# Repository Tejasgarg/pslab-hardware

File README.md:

# PSLab-Mini-hardware

This branch is dedicated to prototyping the PSLab-Mini board and push out a working board that has functionalities of oscilloscope, multimeter and if time allows it, a logic analyser.

## PCB Layout
* I made a new PCB layout by first updating and removing components from the PSLab Schematic.
* The changed schematic was imported into a fresh PCB editor file in KiCAD.
* Made new edge cuts that provide a smaller footprint to the board compared to the current board
* Placed all the components and made a 4-layer PCB
* The 4 layers are as follows:
     * F.Cu(Front Copper) - Consists of signal routings
     * GND(Ground) - Consists of a ground pour in the entire layer
     * VDDA(Power) - Consists of a copper pour that transmits power to the majority of the components
     * B.Cu(Bottom Copper) - Also consists of the routing
* Used both through and buried vias:
     * Buried Vias - Used buried vias for connecting the components to the ground and power layer
     * Through Vias - Used Through vias for connecting the top and bottom copper layer for essentially connecting and routing wherever there was a blockage 
       due to already present routes

Front Side                        | Back Side
 -------------------------------- | ----------------------------------
 | 

## New Schematic
The new schematic has been made on top of the current schematic for a quicker prototype and clearly shows all the components removed in the current PSLab board, and explains the reasoning behind the removal of each. 

## Platform

* Microcontroller Platform : [PIC24EP256GP204](http://www.microchip.com/wwwproducts/en/PIC24EP256GP204)
* IDE: [MPLABX IDE v3.35](http://www.microchip.com/mplab/mplab-x-ide) (Supported on Linux/Windows/Mac)
* Compiler: [MPLAB® XC16 Compiler](http://www.microchip.com/mplab/compilers)
* Programming Tool: [PICkit™ 3 In-Circuit Debugger](http://www.microchip.com/Developmenttools/ProductDetails.aspx?PartNO=PG164130)

## New parts list

* [PIC24EP256GP204](http://www.microchip.com/wwwproducts/en/PIC24EP256GP204) - Microcontroller
* [MCP6S21](http://www.microchip.com/wwwproducts/en/mcp6s21) - Programmable gain amplifier
* [TL082](http://www.ti.com/product/TL082) - 2 channel Op-Amp
* [CP2102N-A02-GQFN24](https://www.silabs.com/documents/public/data-sheets/cp2102n-datasheet.pdf) - USB-UART bridge
* [SP0503BAHTG](https://m.littelfuse.com/~/media/electronics/datasheets/tvs_diode_arrays/littelfuse_tvs_diode_array_sp05_datasheet.pdf.pdf) - ESD protector

* 0.5 A Fuse
* Assorted resistors, capacitors & diodes

## Hardware Specs

* 3-Channel up to 2MSPS Oscilloscope. Software selectable amplification stages
* 12-bit Voltmeter. Input ranges from +/-10 mV to +/-16 V
* Capacitance Measurement. pF to uF range
* UART data buses for secondary modules 

## Feature list for PSLab-Mini

### Oscilloscopes

One of the main features of PSLab is the 3-channel Oscilloscope, which can monitor analog inputs at a maximum of 2 million samples per second.
In PSLab mini, this will be retained but with the following changes:
* Reduce the channels from 3 to 2 channels oscilloscope to reduce the components and cost
* Aim at increasing the max sampling rate

### Measurement Functions

* Frequency counter tested up to 16 MHz.
* Capacitance Measurement. pF to uF range
* Resistance measurement
* Voltmeter with a range of +/-10 mV to +/-16 V

### Other useful tools

* UART outputs
* Graphical Interfaces for Oscilloscope, Multimeter, streaming data and several experiments developed that use a common framework which drastically reduces code required to incorporate control and plotting widgets.

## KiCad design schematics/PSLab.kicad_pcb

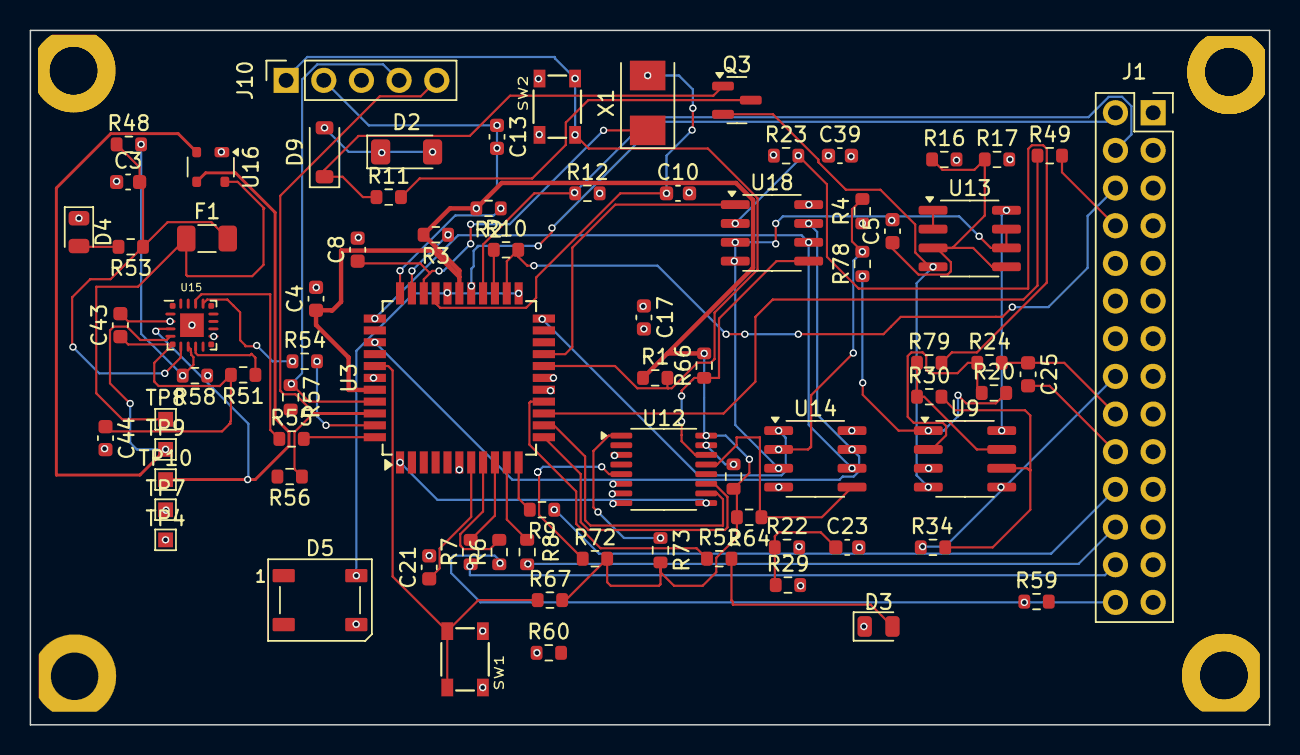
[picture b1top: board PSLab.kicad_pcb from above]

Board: 4 copper layers, 83.6 x 46.8 mm, 82 parts (0 on the bottom side), 71 nets.

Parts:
C3, C4, C13, C17, C25, C39, C43: 100nF; C_0603_1608Metric
C5, C23: 10nF; C_0603_1608Metric
C8, C10: 12pF; C_0603_1608Metric
C21, C44: 10uF; C_0603_1608Metric
D2: 6.8V; D_MiniMELF
D3: GREEN; LED_0805_2012Metric
D4: BLUE; LED_0805_2012Metric
D5: WS2812B; LED_WS2812B_PLCC4_5.0x5.0mm_P3.2mm
D9: 1N4148W; D_SOD-123
F1: 1A; Fuse_1206_3216Metric
J1: DoublePins; PinSocket_2x14_P2.54mm_Vertical
J10: Programmer; PinSocket_1x05_P2.54mm_Vertical
MH4, MH4#2, MH4#3, MH4#4: M; TwoSided_MPad
Q3: MMBT3906; SOT-23
R1, R4, R10, R16, R17, R23, R29, R58, R64, R66, R67, R71, R72, R73, R78, R79: 10k; R_0603_1608Metric
R2, R3, R12, R48, R52, R53, R59, R60: 5.1k; R_0603_1608Metric
R6, R7, R8, R9, R49: 200; R_0603_1608Metric
R11, R51: 1k; R_0603_1608Metric
R20, R30: 200k; R_0603_1608Metric
R22: 12k; R_0603_1608Metric
R24, R34: 1M; R_0603_1608Metric
R54, R55, R56, R57: 18; R_0603_1608Metric
SW1, SW2: SW_MEC_5E; button_SPST_3x4x2.5
TP4, TP7: GND; TestPoint_Pad_1.0x1.0mm
TP8: VBUS; TestPoint_Pad_1.0x1.0mm
TP9: D-; TestPoint_Pad_1.0x1.0mm
TP10: D+; TestPoint_Pad_1.0x1.0mm
U3: PIC24EP256GP204; TQFP-44_10x10mm_P0.8mm
U9, U13: TL082; SOIC-8_3.9x4.9mm_P1.27mm
U12: 74HC4051; TSSOP-16_4.4x5mm_P0.65mm
U14, U18: MCP6S21; SOIC-8_3.9x4.9mm_P1.27mm
U15: CP2102N-xxx-xQFN20x; QFN-20_EP_3x3_Pitch0.5mm
U16: SP0503BAHT; SOT-143
X1: 12MHz; Crystal_SMD_5032-2Pin_5.0x3.2mm

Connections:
+3.3V: C4.1, C13.1, J10.2, R1.1, R2.2, R3.2, R64.2, R66.2, R67.2, R71.2, R72.2, R73.2, U3.28 (VDD), U3.40 (VDD), U12.16 (VCC)
+6V: U9.8 (V+), U13.8 (V+)
-6V: Q3.2 (E), U9.4 (V-), U13.4 (V-)
-9V: Q3.3 (C), R11.2
/CAP: J1.6, R10.2, U3.24 (PGED1|AN5|C1IN1-|RP35|RB3)
/CP2102_Vreg: C43.1, C44.1, R51.2, U15.6 (VDD)
/D+: TP10.1, U15.4 (D+), U16.3 (K)
/D-: TP9.1, U15.5 (D-), U16.2 (K)
/LA1_: R6.2, U3.8 (RP42|RB10)
/LA2_: R7.2, U3.9 (RP43|RB11)
/LA3_: R8.2, U3.10 (RPI44|RB12)
/LA4_: R9.2, U3.11 (RPI45|CTPLS|RB13)
/OSC_IN: C10.1, U3.30 (OSC1|CLKI|RA2), X1.2
/OSC_OUT: C8.1, U3.31 (OSC2|CLKO|RA3), X1.1
/OSC_REF1: U13.6 (-), U13.7, U14.3 (VREF), U18.3 (VREF)
/OSC_REF2: C23.1, R22.1, R29.1
/RES: J1.4, R12.1, U3.26 (AN7|C3IN1-|C4IN1-|RC1)
/RxD: R54.2, U3.43 (RP39|INT0|RB7)
/SCL: R2.1, U3.33 (SCL2|RP36|RB4)
/SDA: R3.1, U3.32 (SDA2|RPI24|RA8)
/TxD: R55.2, U3.44 (TCK|ASCL1|RP40|T4CK|RB8)
/VBusSense: R48.2, R58.2, U15.8 (VBUS)
/VINPUT: C3.2, F1.2, R48.1, R53.1, U15.7 (VregIn)
/VOL: J1.2, U3.27 (AN8|C3IN1+|RC2)
/VUSBIN: F1.1, TP8.1, U16.4 (K)
ACH1: C25.2, J1.20
BOOT: R67.1, SW1.1, SW1.2, U3.38 (SCL1|RPI53|RC5)
CH1: C25.1, J1.18, R24.2
CH1_IN: U3.22 (PGEC3|AN3|OA1OUT|RPI33|RB1), U14.1 (OUT)
CH2: J1.16, R34.1
CH2_IN: U3.19 (AN0|OA2OUT|RA0), U18.1 (OUT)
CS1: R64.1, U12.13 (A0), U14.5 (CS)
CS2: R66.1, U12.14 (A1), U18.5 (CS)
CS3: R71.1, U12.15 (A2)
CS.CH1: U3.12 (TDO|RA10), U12.11 (S0)
CS.CH2: U3.13 (TDI|RA7), U12.10 (S1)
CS.CH3: U3.1 (TMS|ASDA1|RP41|RB9), U12.9 (S2)
FQy: J1.8, R49.2
GND: C3.1, C4.2, C5.2, C8.2, C10.2, C13.2, C17.2, C21.2, C23.2, C39.2, C43.2, C44.2, D2.1 (K), D3.1 (K), D4.1 (K), D5.3 (VSS), J1.1, J1.3, J1.5, J1.7, J1.9, J1.11, J1.13, J1.15, J1.17, J1.19, J1.21, J1.23, J1.25, J1.27, J10.3, MH4.1, MH4#2.1, MH4#3.1, MH4#4.1, R17.2, R29.2, R58.1, R59.1, R60.1, SW1.3 (K), SW1.4 (A), SW2.3 (K), SW2.4 (A), TP4.1, TP7.1, U3.6 (GND), U3.16 (GND), U3.29 (GND), U3.39 (GND), U9.3 (+), U9.5 (+), U12.3 (A), U12.6 (~E), U12.7 (VEE), U12.8 (GND), U14.4 (GND), U15.3 (GND), U15.12 (GND), U15.21 (GND), U16.1 (A), U18.4 (GND)
LA1: J1.28, R6.1
LA2: J1.26, R7.1
LA3: J1.24, R8.1
LA4: J1.22, R9.1
MCLR: J10.1, R1.2, SW2.1, SW2.2, U3.18 (~MCLR)
unnamed: D2.2 (A), D9.2 (A)
unnamed: D3.2 (A), R52.2
unnamed: D4.2 (A), R53.2
unnamed: D9.1 (K), Q3.1 (B), R11.1
unnamed: R20.2, R78.1, U9.1
unnamed: R30.1, R79.1, U9.7
unnamed: R10.1, U3.25 (AN6|OA3OUT|C4IN1+|RC0)
unnamed: R49.1, U3.14 (RPI46|T3CK|RB14)
unnamed: C21.1, U3.7 (VCAP)
unnamed: R20.1, R24.1, U9.2 (-)
unnamed: R30.2, R34.2, U9.6 (-)
unnamed: R72.1, U12.5 (A5)
unnamed: C5.1, R16.1, R17.1, U13.3 (+), U13.5 (+)
unnamed: U13.1, U13.2 (-)
unnamed: R4.2, R78.2, U14.2 (CHA)
unnamed: R51.1, U15.9 (RSTb)
unnamed: R54.1, U15.17 (RXD)
unnamed: R55.1, U15.18 (TXD)
unnamed: R23.2, R79.2, U18.2 (CHA)
PGC2: J10.5, R56.1, U3.42 (PGEC2|ASCL2|RP38|RB6)
PGD2: J10.4, R57.1, U3.41 (PGED2|ASDA2|RP37|RB5)
RGB: D5.4 (DIN), U3.23 (PGEC1|AN4|C1IN1+|RPI34|RB2)
SCK: U3.36 (SCK1|RPI51|RC3), U14.7 (SCK), U18.7 (SCK)
SDO: U3.34 (SDO1|RP20|T1CK|RA4), U14.6 (SDI), U18.6 (SDI)
SPI.CS: R73.1, U12.1 (A4)
STAT: R52.1, U3.15 (RPI47|T5CK|RB15)
VDDA: C17.1, C39.1, R4.1, R12.2, R16.2, R22.2, R23.1, U3.17 (AVDD), U14.8 (VDD), U18.8 (VDD)

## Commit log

2025-04-08 feat: PSLab Mini prototype v1.0
2025-04-08 fixup
